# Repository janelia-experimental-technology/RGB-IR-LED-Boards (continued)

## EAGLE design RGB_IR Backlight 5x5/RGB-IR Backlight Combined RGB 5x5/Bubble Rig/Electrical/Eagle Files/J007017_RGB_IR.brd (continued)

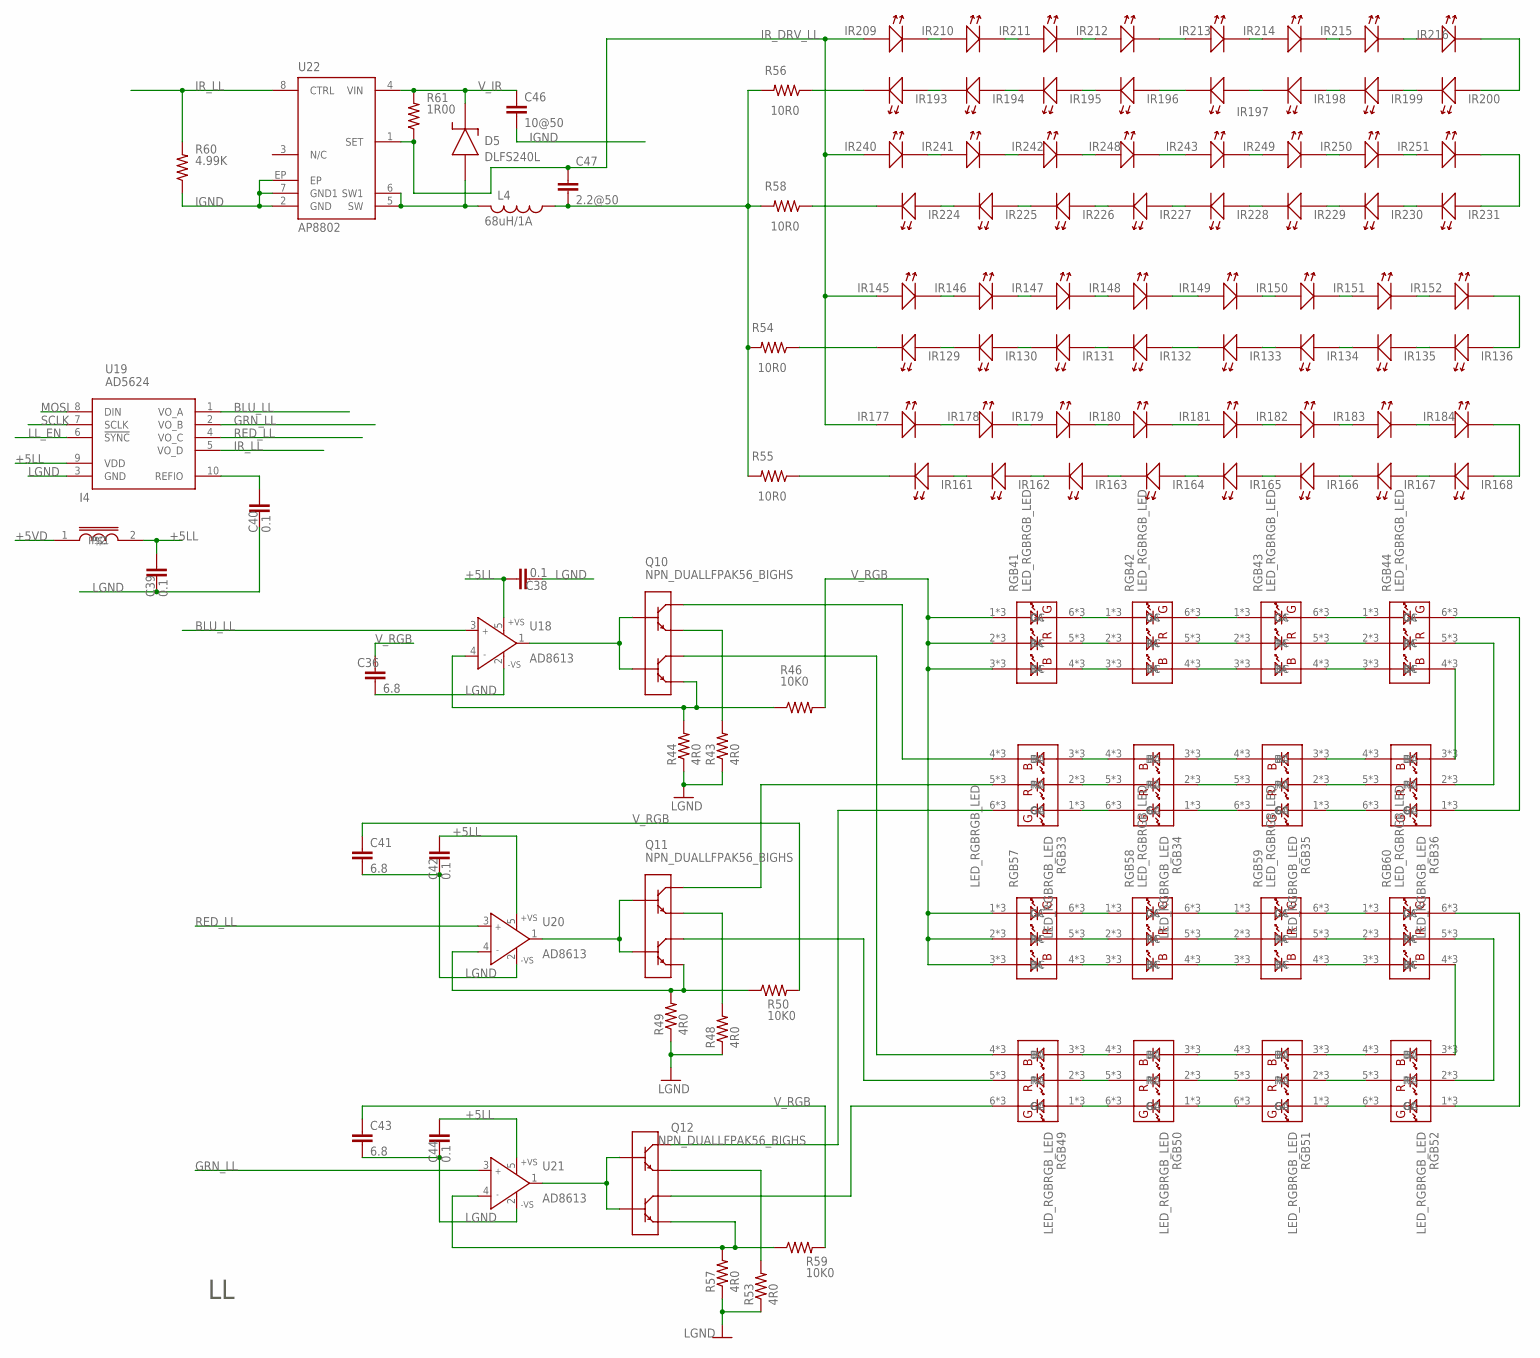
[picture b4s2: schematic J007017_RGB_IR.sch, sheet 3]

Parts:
C36, C41, C43: 6.8; 1210S
C38, C39, C40, C42, C44: 0.1; 0603S
C46: 10@50; 1210S
C47: 2.2@50; 1206S
D5: DLFS240L; PWRDI-123
I4: INDUCTOR0805S; 0805S
IR129: LEDLED_SFH4050_A; LED_SFH4045_HEAT_A
IR130, IR131, IR132, IR133, IR134, IR135, IR145, IR146, IR147, IR148, IR149, IR150, IR151, IR152, IR161, IR162, IR163, IR164, IR165, IR166, IR167, IR168, IR177, IR178, IR179, IR180, IR181, IR182, IR183, IR184, IR193, IR194, IR195, IR196, IR197, IR198, IR199, IR200, IR209, IR210, IR211, IR212, IR213, IR214, IR215, IR216, IR224, IR225, IR226, IR227, IR228, IR229, IR230, IR231, IR240, IR241, IR242, IR243, IR248, IR249, IR250: LEDLED_SFH4050_HEAT; LED_SFH4050_HEAT
IR136, IR251: LEDLED_SFH4050; LED_SFH4050
L4: 68uH/1A; SRU8043
Q10, Q11, Q12: NPN_DUALLFPAK56_BIGHS; LFPAK56_HS2
R43, R44, R48, R49, R53, R57: 4R0; 1812
R46, R50, R59: 10K0; 1206S
R54, R55, R56, R58: 10R0; 1206S
R60: 4.99K; 0805S
R61: 1R00; 1206S
RGB33, RGB34, RGB35, RGB36, RGB41, RGB42, RGB43, RGB44, RGB49, RGB50, RGB51, RGB52, RGB57, RGB58, RGB59, RGB60: LED_RGBRGB_LED; OVSPRGB_HS_FIXED
U18, U20, U21: AD8613; SOT23-5
U19: AD5624; MSOP10
U22: AP8802; SOIC8-EP

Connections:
+5LL: C38.1, C39.1, C42.1, C44.1, I4.2, U18.5 (+VS), U19.9 (VDD), U20.5 (+VS), U21.5 (+VS)
+5VD: I4.1; also elsewhere on the board
BLU_LL: U18.3 (IN+), U19.1 (VO_A)
GRN_LL: U19.2 (VO_B), U21.3 (IN+)
IGND: C46.2, R60.1, U22.2 (GND), U22.7 (GND1), U22.EP; also elsewhere on the board
IR_DRV_LL: C47.1, IR145.A, IR145.A1 (A), IR177.A, IR177.A1 (A), IR209.A, IR209.A1 (A), IR240.A, IR240.A1 (A), R61.1, U22.1 (SET)
IR_LL: R60.2, U19.5 (VO_D), U22.8 (CTRL)
IR_RET_UL1: C47.2, L4.1, R54.2, R55.2, R56.2, R58.2
LGND: C36.2, C38.2, C39.2, C40.2, C41.2, C42.2, C43.2, C44.2, R43.1, R44.1, R48.1, R49.1, R53.1, R57.1, U18.2 (-VS), U19.3 (GND), U20.2 (-VS), U21.2 (-VS); also elsewhere on the board
LL_EN: U19.6 (!SYNC); also elsewhere on the board
MOSI: U19.8 (DIN); also elsewhere on the board
unnamed: IR135.A, IR135.A1 (A), IR136.C (K)
unnamed: IR134.A, IR134.A1 (A), IR135.C (K), IR135.C1 (K)
unnamed: IR133.A, IR133.A1 (A), IR134.C (K), IR134.C1 (K)
unnamed: C40.1, U19.10 (REFIO)
unnamed: IR131.A, IR131.A1 (A), IR132.C (K), IR132.C1 (K)
unnamed: IR130.A, IR130.A1 (A), IR131.C (K), IR131.C1 (K)
unnamed: IR129.A, IR129.A1 (A), IR130.C (K), IR130.C1 (K)
unnamed: IR145.C (K), IR145.C1 (K), IR146.A, IR146.A1 (A)
unnamed: IR146.C (K), IR146.C1 (K), IR147.A, IR147.A1 (A)
unnamed: IR147.C (K), IR147.C1 (K), IR148.A, IR148.A1 (A)
unnamed: IR132.A, IR132.A1 (A), IR133.C (K), IR133.C1 (K)
unnamed: IR167.A, IR167.A1 (A), IR168.C (K), IR168.C1 (K)
unnamed: IR166.A, IR166.A1 (A), IR167.C (K), IR167.C1 (K)
unnamed: IR165.A, IR165.A1 (A), IR166.C (K), IR166.C1 (K)
unnamed: IR164.A, IR164.A1 (A), IR165.C (K), IR165.C1 (K)
unnamed: IR163.A, IR163.A1 (A), IR164.C (K), IR164.C1 (K)
unnamed: IR162.A, IR162.A1 (A), IR163.C (K), IR163.C1 (K)
unnamed: IR161.A, IR161.A1 (A), IR162.C (K), IR162.C1 (K)
unnamed: IR149.C (K), IR149.C1 (K), IR150.A, IR150.A1 (A)
unnamed: IR150.C (K), IR150.C1 (K), IR151.A, IR151.A1 (A)
unnamed: IR151.C (K), IR151.C1 (K), IR152.A, IR152.A1 (A)
unnamed: IR177.C (K), IR177.C1 (K), IR178.A, IR178.A1 (A)
unnamed: IR178.C (K), IR178.C1 (K), IR179.A, IR179.A1 (A)
unnamed: IR179.C (K), IR179.C1 (K), IR180.A, IR180.A1 (A)
unnamed: IR181.C (K), IR181.C1 (K), IR182.A, IR182.A1 (A)
unnamed: IR182.C (K), IR182.C1 (K), IR183.A, IR183.A1 (A)
unnamed: IR183.C (K), IR183.C1 (K), IR184.A, IR184.A1 (A)
unnamed: IR148.C (K), IR148.C1 (K), IR149.A, IR149.A1 (A)
unnamed: IR136.A, IR152.C (K), IR152.C1 (K)
unnamed: IR180.C (K), IR180.C1 (K), IR181.A, IR181.A1 (A)
unnamed: IR168.A, IR168.A1 (A), IR184.C (K), IR184.C1 (K)
unnamed: IR129.C (K), R54.1
unnamed: IR161.C (K), IR161.C1 (K), R55.1
unnamed: IR199.A, IR199.A1 (A), IR200.C (K), IR200.C1 (K)
unnamed: IR198.A, IR198.A1 (A), IR199.C (K), IR199.C1 (K)
unnamed: IR197.A, IR197.A1 (A), IR198.C (K), IR198.C1 (K)
unnamed: IR195.A, IR195.A1 (A), IR196.C (K), IR196.C1 (K)
unnamed: IR194.A, IR194.A1 (A), IR195.C (K), IR195.C1 (K)
unnamed: IR193.A, IR193.A1 (A), IR194.C (K), IR194.C1 (K)
unnamed: IR209.C (K), IR209.C1 (K), IR210.A, IR210.A1 (A)
unnamed: IR210.C (K), IR210.C1 (K), IR211.A, IR211.A1 (A)
unnamed: IR211.C (K), IR211.C1 (K), IR212.A, IR212.A1 (A)
unnamed: IR196.A, IR196.A1 (A), IR197.C (K), IR197.C1 (K)
unnamed: IR230.A, IR230.A1 (A), IR231.C (K), IR231.C1 (K)
unnamed: IR229.A, IR229.A1 (A), IR230.C (K), IR230.C1 (K)
unnamed: IR228.A, IR228.A1 (A), IR229.C (K), IR229.C1 (K)
unnamed: IR227.A, IR227.A1 (A), IR228.C (K), IR228.C1 (K)
unnamed: IR226.A, IR226.A1 (A), IR227.C (K), IR227.C1 (K)
unnamed: IR225.A, IR225.A1 (A), IR226.C (K), IR226.C1 (K)
unnamed: IR224.A, IR224.A1 (A), IR225.C (K), IR225.C1 (K)
unnamed: IR213.C (K), IR213.C1 (K), IR214.A, IR214.A1 (A)
unnamed: IR214.C (K), IR214.C1 (K), IR215.A, IR215.A1 (A)
unnamed: IR215.C (K), IR215.C1 (K), IR216.A, IR216.A1 (A)
unnamed: IR240.C (K), IR240.C1 (K), IR241.A, IR241.A1 (A)
unnamed: IR241.C (K), IR241.C1 (K), IR242.A, IR242.A1 (A)
unnamed: IR242.C (K), IR242.C1 (K), IR248.A, IR248.A1 (A)
unnamed: IR243.C (K), IR243.C1 (K), IR249.A, IR249.A1 (A)
unnamed: IR249.C (K), IR249.C1 (K), IR250.A, IR250.A1 (A)
unnamed: IR250.C (K), IR250.C1 (K), IR251.A
unnamed: IR212.C (K), IR212.C1 (K), IR213.A, IR213.A1 (A)
unnamed: IR200.A, IR200.A1 (A), IR216.C (K), IR216.C1 (K)
unnamed: IR243.A, IR243.A1 (A), IR248.C (K), IR248.C1 (K)
unnamed: IR231.A, IR231.A1 (A), IR251.C (K)
unnamed: IR193.C (K), IR193.C1 (K), R56.1
unnamed: IR224.C (K), IR224.C1 (K), R58.1
unnamed: Q10.3 (E2), R44.2, R46.1, U18.4 (IN-)
unnamed: D5.A, L4.2, U22.5 (SW), U22.6 (SW1)
unnamed: Q11.3 (E2), R49.2, R50.1, U20.4 (IN-)
unnamed: Q11.2 (B1), Q11.4 (B2), U20.1 (OUT)
unnamed: RGB41.6 (GC), RGB41.6A (GC), RGB41.6B (GC), RGB42.1 (GA), RGB42.1A (GA), RGB42.1B (GA)
unnamed: RGB41.5 (RC), RGB41.5A (RC), RGB41.5B (RC), RGB42.2 (RA), RGB42.2A (RA), RGB42.2B (RA)
unnamed: RGB41.4 (BC), RGB41.4A (BC), RGB41.4B (BC), RGB42.3 (BA), RGB42.3A (BA), RGB42.3B (BA)
unnamed: RGB42.6 (GC), RGB42.6A (GC), RGB42.6B (GC), RGB43.1 (GA), RGB43.1A (GA), RGB43.1B (GA)
unnamed: RGB42.5 (RC), RGB42.5A (RC), RGB42.5B (RC), RGB43.2 (RA), RGB43.2A (RA), RGB43.2B (RA)
unnamed: RGB42.4 (BC), RGB42.4A (BC), RGB42.4B (BC), RGB43.3 (BA), RGB43.3A (BA), RGB43.3B (BA)
unnamed: RGB43.6 (GC), RGB43.6A (GC), RGB43.6B (GC), RGB44.1 (GA), RGB44.1A (GA), RGB44.1B (GA)
unnamed: RGB43.5 (RC), RGB43.5A (RC), RGB43.5B (RC), RGB44.2 (RA), RGB44.2A (RA), RGB44.2B (RA)
unnamed: RGB43.4 (BC), RGB43.4A (BC), RGB43.4B (BC), RGB44.3 (BA), RGB44.3A (BA), RGB44.3B (BA)
unnamed: RGB36.1 (GA), RGB36.1A (GA), RGB36.1B (GA), RGB44.6 (GC), RGB44.6A (GC), RGB44.6B (GC)
unnamed: RGB36.2 (RA), RGB36.2A (RA), RGB36.2B (RA), RGB44.5 (RC), RGB44.5A (RC), RGB44.5B (RC)
unnamed: RGB36.3 (BA), RGB36.3A (BA), RGB36.3B (BA), RGB44.4 (BC), RGB44.4A (BC), RGB44.4B (BC)
unnamed: RGB35.1 (GA), RGB35.1A (GA), RGB35.1B (GA), RGB36.6 (GC), RGB36.6A (GC), RGB36.6B (GC)
unnamed: RGB35.2 (RA), RGB35.2A (RA), RGB35.2B (RA), RGB36.5 (RC), RGB36.5A (RC), RGB36.5B (RC)
unnamed: RGB35.3 (BA), RGB35.3A (BA), RGB35.3B (BA), RGB36.4 (BC), RGB36.4A (BC), RGB36.4B (BC)
unnamed: RGB34.1 (GA), RGB34.1A (GA), RGB34.1B (GA), RGB35.6 (GC), RGB35.6A (GC), RGB35.6B (GC)
unnamed: RGB34.2 (RA), RGB34.2A (RA), RGB34.2B (RA), RGB35.5 (RC), RGB35.5A (RC), RGB35.5B (RC)
unnamed: RGB34.3 (BA), RGB34.3A (BA), RGB34.3B (BA), RGB35.4 (BC), RGB35.4A (BC), RGB35.4B (BC)
unnamed: RGB33.1 (GA), RGB33.1A (GA), RGB33.1B (GA), RGB34.6 (GC), RGB34.6A (GC), RGB34.6B (GC)
unnamed: RGB33.2 (RA), RGB33.2A (RA), RGB33.2B (RA), RGB34.5 (RC), RGB34.5A (RC), RGB34.5B (RC)
unnamed: RGB33.3 (BA), RGB33.3A (BA), RGB33.3B (BA), RGB34.4 (BC), RGB34.4A (BC), RGB34.4B (BC)
unnamed: Q12.3 (E2), R57.2, R59.1, U21.4 (IN-)
unnamed: Q12.2 (B1), Q12.4 (B2), U21.1 (OUT)
unnamed: RGB57.6 (GC), RGB57.6A (GC), RGB57.6B (GC), RGB58.1 (GA), RGB58.1A (GA), RGB58.1B (GA)
unnamed: RGB57.5 (RC), RGB57.5A (RC), RGB57.5B (RC), RGB58.2 (RA), RGB58.2A (RA), RGB58.2B (RA)
unnamed: RGB57.4 (BC), RGB57.4A (BC), RGB57.4B (BC), RGB58.3 (BA), RGB58.3A (BA), RGB58.3B (BA)
unnamed: RGB58.6 (GC), RGB58.6A (GC), RGB58.6B (GC), RGB59.1 (GA), RGB59.1A (GA), RGB59.1B (GA)
unnamed: RGB58.5 (RC), RGB58.5A (RC), RGB58.5B (RC), RGB59.2 (RA), RGB59.2A (RA), RGB59.2B (RA)
unnamed: RGB58.4 (BC), RGB58.4A (BC), RGB58.4B (BC), RGB59.3 (BA), RGB59.3A (BA), RGB59.3B (BA)
unnamed: RGB59.6 (GC), RGB59.6A (GC), RGB59.6B (GC), RGB60.1 (GA), RGB60.1A (GA), RGB60.1B (GA)
unnamed: RGB59.5 (RC), RGB59.5A (RC), RGB59.5B (RC), RGB60.2 (RA), RGB60.2A (RA), RGB60.2B (RA)
unnamed: RGB59.4 (BC), RGB59.4A (BC), RGB59.4B (BC), RGB60.3 (BA), RGB60.3A (BA), RGB60.3B (BA)
unnamed: RGB52.1 (GA), RGB52.1A (GA), RGB52.1B (GA), RGB60.6 (GC), RGB60.6A (GC), RGB60.6B (GC)
unnamed: RGB52.2 (RA), RGB52.2A (RA), RGB52.2B (RA), RGB60.5 (RC), RGB60.5A (RC), RGB60.5B (RC)
unnamed: RGB52.3 (BA), RGB52.3A (BA), RGB52.3B (BA), RGB60.4 (BC), RGB60.4A (BC), RGB60.4B (BC)
unnamed: RGB51.1 (GA), RGB51.1A (GA), RGB51.1B (GA), RGB52.6 (GC), RGB52.6A (GC), RGB52.6B (GC)
unnamed: RGB51.2 (RA), RGB51.2A (RA), RGB51.2B (RA), RGB52.5 (RC), RGB52.5A (RC), RGB52.5B (RC)
unnamed: RGB51.3 (BA), RGB51.3A (BA), RGB51.3B (BA), RGB52.4 (BC), RGB52.4A (BC), RGB52.4B (BC)
unnamed: RGB50.1 (GA), RGB50.1A (GA), RGB50.1B (GA), RGB51.6 (GC), RGB51.6A (GC), RGB51.6B (GC)
unnamed: RGB50.2 (RA), RGB50.2A (RA), RGB50.2B (RA), RGB51.5 (RC), RGB51.5A (RC), RGB51.5B (RC)
unnamed: RGB50.3 (BA), RGB50.3A (BA), RGB50.3B (BA), RGB51.4 (BC), RGB51.4A (BC), RGB51.4B (BC)
unnamed: RGB49.1 (GA), RGB49.1A (GA), RGB49.1B (GA), RGB50.6 (GC), RGB50.6A (GC), RGB50.6B (GC)
unnamed: RGB49.2 (RA), RGB49.2A (RA), RGB49.2B (RA), RGB50.5 (RC), RGB50.5A (RC), RGB50.5B (RC)
unnamed: RGB49.3 (BA), RGB49.3A (BA), RGB49.3B (BA), RGB50.4 (BC), RGB50.4A (BC), RGB50.4B (BC)
unnamed: Q10.2 (B1), Q10.4 (B2), U18.1 (OUT)
unnamed: Q10.1 (E1), R43.2
unnamed: Q11.1 (E1), R48.2
unnamed: Q12.1 (E1), R53.2
Q4A: Q10.7 (C1), Q10.8 (C1), Q10.8A (C1), Q10.8B (C1), Q10.8C (C1), Q10.8C1 (C1), Q10.8C2 (C1), Q10.8C3 (C1), Q10.78 (C1), Q10.78A (C1), Q10.78B (C1), RGB33.4 (BC), RGB33.4A (BC), RGB33.4B (BC)
Q4B: Q10.5 (C2), Q10.5A (C2), Q10.5A1 (C2), Q10.5B (C2), Q10.5C (C2), Q10.5C1 (C2), Q10.5C2 (C2), Q10.6 (C2), Q10.56 (C2), Q10.56A (C2), Q10.56B (C2), RGB49.4 (BC), RGB49.4A (BC), RGB49.4B (BC)
Q5A: Q11.7 (C1), Q11.8 (C1), Q11.8A (C1), Q11.8B (C1), Q11.8C (C1), Q11.8C1 (C1), Q11.8C2 (C1), Q11.8C3 (C1), Q11.78 (C1), Q11.78A (C1), Q11.78B (C1), RGB33.5 (RC), RGB33.5A (RC), RGB33.5B (RC)
Q5B: Q11.5 (C2), Q11.5A (C2), Q11.5A1 (C2), Q11.5B (C2), Q11.5C (C2), Q11.5C1 (C2), Q11.5C2 (C2), Q11.6 (C2), Q11.56 (C2), Q11.56A (C2), Q11.56B (C2), RGB49.5 (RC), RGB49.5A (RC), RGB49.5B (RC)
Q6A: Q12.7 (C1), Q12.8 (C1), Q12.8A (C1), Q12.8B (C1), Q12.8C (C1), Q12.8C1 (C1), Q12.8C2 (C1), Q12.8C3 (C1), Q12.78 (C1), Q12.78A (C1), Q12.78B (C1), RGB33.6 (GC), RGB33.6A (GC), RGB33.6B (GC)
Q6B: Q12.5 (C2), Q12.5A (C2), Q12.5A1 (C2), Q12.5B (C2), Q12.5C (C2), Q12.5C1 (C2), Q12.5C2 (C2), Q12.6 (C2), Q12.56 (C2), Q12.56A (C2), Q12.56B (C2), RGB49.6 (GC), RGB49.6A (GC), RGB49.6B (GC)
RED_LL: U19.4 (VO_C), U20.3 (IN+)
SCLK: U19.7 (SCLK); also elsewhere on the board
V_IR: C46.1, D5.K, R61.2, U22.4 (VIN); also elsewhere on the board
V_RGB: C36.1, C41.1, C43.1, R46.2, R50.2, R59.2, RGB41.1 (GA), RGB41.1A (GA), RGB41.1B (GA), RGB41.2 (RA), RGB41.2A (RA), RGB41.2B (RA), RGB41.3 (BA), RGB41.3A (BA), RGB41.3B (BA), RGB57.1 (GA), RGB57.1A (GA), RGB57.1B (GA), RGB57.2 (RA), RGB57.2A (RA), RGB57.2B (RA), RGB57.3 (BA), RGB57.3A (BA), RGB57.3B (BA); also elsewhere on the board

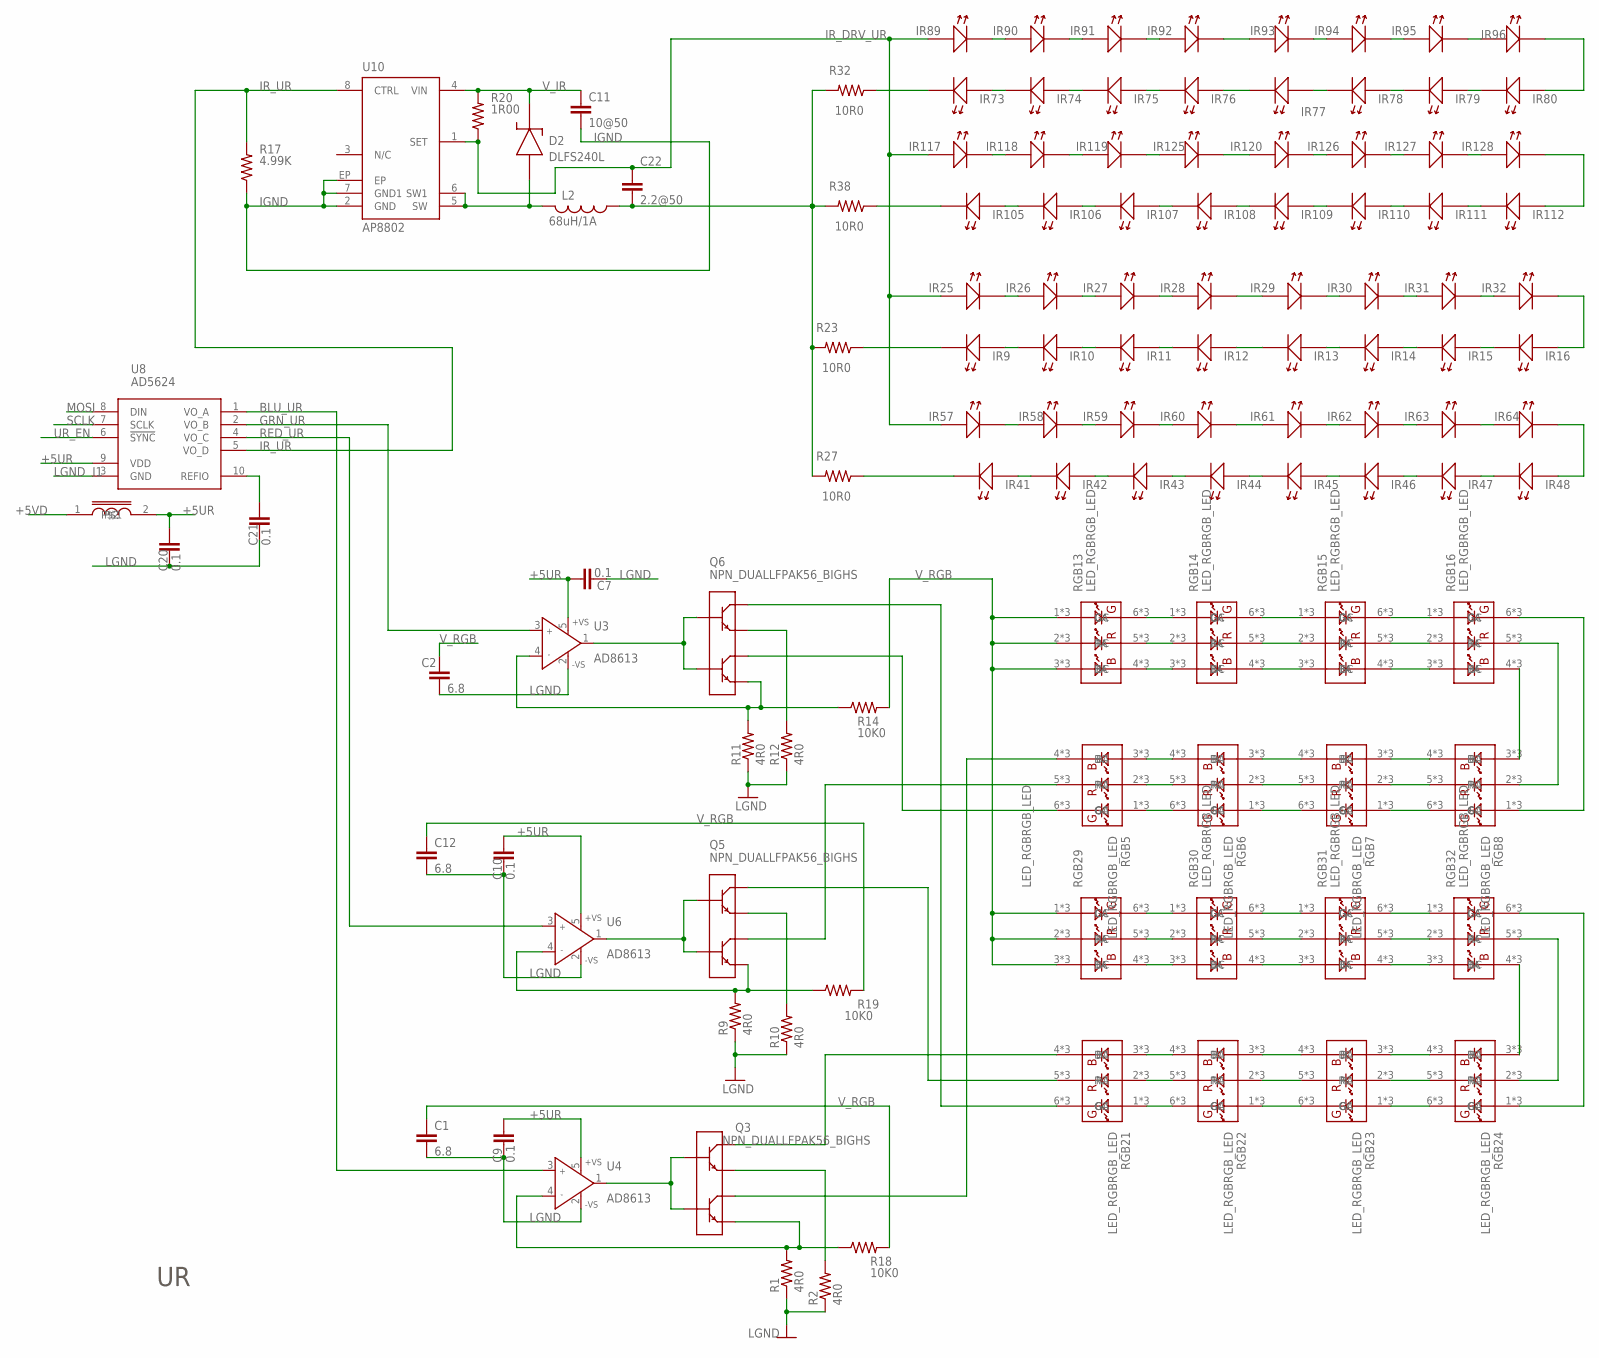
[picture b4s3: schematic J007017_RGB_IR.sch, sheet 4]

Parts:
C1, C2, C12: 6.8; 1210S
C7, C9, C10, C20, C21: 0.1; 0603S
C11: 10@50; 1210S
C22: 2.2@50; 1206S
D2: DLFS240L; PWRDI-123
I1: INDUCTOR0805S; 0805S
IR9, IR10, IR11, IR12, IR13, IR14, IR15, IR16, IR25, IR26, IR27, IR28, IR29, IR30, IR31, IR32, IR41, IR42, IR43, IR44, IR45, IR46, IR47, IR48, IR57, IR58, IR59, IR60, IR61, IR62, IR63, IR64, IR73, IR74, IR75, IR76, IR77, IR78, IR79, IR80, IR89, IR90, IR91, IR92, IR93, IR94, IR95, IR96, IR105, IR107, IR108, IR109, IR110, IR111, IR112, IR118, IR119, IR120, IR125, IR126, IR127: LEDLED_SFH4050_HEAT; LED_SFH4050_HEAT
IR106: LEDLED_SFH4050_C; LED_SFH4050_HEAT_C
IR117, IR128: LEDLED_SFH4050; LED_SFH4050
L2: 68uH/1A; SRU8043
Q3, Q5, Q6: NPN_DUALLFPAK56_BIGHS; LFPAK56_HS2
R1, R2, R9, R10, R11, R12: 4R0; 1812
R14, R18, R19: 10K0; 1206S
R17: 4.99K; 0805S
R20: 1R00; 1206S
R23, R27, R32, R38: 10R0; 1206S
RGB5, RGB6, RGB7, RGB8, RGB13, RGB14, RGB15, RGB16, RGB21, RGB22, RGB23, RGB24, RGB29, RGB30, RGB31, RGB32: LED_RGBRGB_LED; OVSPRGB_HS_FIXED
U3, U4, U6: AD8613; SOT23-5
U8: AD5624; MSOP10
U10: AP8802; SOIC8-EP

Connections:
+5UR: C7.1, C9.1, C10.1, C20.1, I1.2, U3.5 (+VS), U4.5 (+VS), U6.5 (+VS), U8.9 (VDD)
+5VD: I1.1; also elsewhere on the board
BLU_UR: U4.3 (IN+), U8.1 (VO_A)
GRN_UR: U3.3 (IN+), U8.2 (VO_B)
IGND: C11.2, R17.1, U10.2 (GND), U10.7 (GND1), U10.EP; also elsewhere on the board
IR_DRV_UR: C22.1, IR25.A, IR25.A1 (A), IR57.A, IR57.A1 (A), IR89.A, IR89.A1 (A), IR117.A, R20.1, U10.1 (SET)
IR_RET_UL2: C22.2, L2.1, R23.2, R27.2, R32.2, R38.2
IR_UR: R17.2, U8.5 (VO_D), U10.8 (CTRL)
LGND: C1.2, C2.2, C7.2, C9.2, C10.2, C12.2, C20.2, C21.2, R1.1, R2.1, R9.1, R10.1, R11.1, R12.1, U3.2 (-VS), U4.2 (-VS), U6.2 (-VS), U8.3 (GND); also elsewhere on the board
MOSI: U8.8 (DIN); also elsewhere on the board
unnamed: C21.1, U8.10 (REFIO)
unnamed: IR15.A, IR15.A1 (A), IR16.C (K), IR16.C1 (K)
unnamed: IR14.A, IR14.A1 (A), IR15.C (K), IR15.C1 (K)
unnamed: IR13.A, IR13.A1 (A), IR14.C (K), IR14.C1 (K)
unnamed: IR11.A, IR11.A1 (A), IR12.C (K), IR12.C1 (K)
unnamed: IR10.A, IR10.A1 (A), IR11.C (K), IR11.C1 (K)
unnamed: IR9.A, IR9.A1 (A), IR10.C (K), IR10.C1 (K)
unnamed: IR25.C (K), IR25.C1 (K), IR26.A, IR26.A1 (A)
unnamed: IR26.C (K), IR26.C1 (K), IR27.A, IR27.A1 (A)
unnamed: IR27.C (K), IR27.C1 (K), IR28.A, IR28.A1 (A)
unnamed: IR12.A, IR12.A1 (A), IR13.C (K), IR13.C1 (K)
unnamed: IR47.A, IR47.A1 (A), IR48.C (K), IR48.C1 (K)
unnamed: IR46.A, IR46.A1 (A), IR47.C (K), IR47.C1 (K)
unnamed: IR45.A, IR45.A1 (A), IR46.C (K), IR46.C1 (K)
unnamed: IR44.A, IR44.A1 (A), IR45.C (K), IR45.C1 (K)
unnamed: IR43.A, IR43.A1 (A), IR44.C (K), IR44.C1 (K)
unnamed: IR42.A, IR42.A1 (A), IR43.C (K), IR43.C1 (K)
unnamed: IR41.A, IR41.A1 (A), IR42.C (K), IR42.C1 (K)
unnamed: IR29.C (K), IR29.C1 (K), IR30.A, IR30.A1 (A)
unnamed: IR30.C (K), IR30.C1 (K), IR31.A, IR31.A1 (A)
unnamed: IR31.C (K), IR31.C1 (K), IR32.A, IR32.A1 (A)
unnamed: IR57.C (K), IR57.C1 (K), IR58.A, IR58.A1 (A)
unnamed: IR58.C (K), IR58.C1 (K), IR59.A, IR59.A1 (A)
unnamed: IR59.C (K), IR59.C1 (K), IR60.A, IR60.A1 (A)
unnamed: IR61.C (K), IR61.C1 (K), IR62.A, IR62.A1 (A)
unnamed: IR62.C (K), IR62.C1 (K), IR63.A, IR63.A1 (A)
unnamed: IR63.C (K), IR63.C1 (K), IR64.A, IR64.A1 (A)
unnamed: IR28.C (K), IR28.C1 (K), IR29.A, IR29.A1 (A)
unnamed: IR16.A, IR16.A1 (A), IR32.C (K), IR32.C1 (K)
unnamed: IR60.C (K), IR60.C1 (K), IR61.A, IR61.A1 (A)
unnamed: IR48.A, IR48.A1 (A), IR64.C (K), IR64.C1 (K)
unnamed: IR9.C (K), IR9.C1 (K), R23.1
unnamed: IR41.C (K), IR41.C1 (K), R27.1
unnamed: IR79.A, IR79.A1 (A), IR80.C (K), IR80.C1 (K)
unnamed: IR78.A, IR78.A1 (A), IR79.C (K), IR79.C1 (K)
unnamed: IR77.A, IR77.A1 (A), IR78.C (K), IR78.C1 (K)
unnamed: IR75.A, IR75.A1 (A), IR76.C (K), IR76.C1 (K)
unnamed: IR74.A, IR74.A1 (A), IR75.C (K), IR75.C1 (K)
unnamed: IR73.A, IR73.A1 (A), IR74.C (K), IR74.C1 (K)
unnamed: IR89.C (K), IR89.C1 (K), IR90.A, IR90.A1 (A)
unnamed: IR90.C (K), IR90.C1 (K), IR91.A, IR91.A1 (A)
unnamed: IR91.C (K), IR91.C1 (K), IR92.A, IR92.A1 (A)
unnamed: IR76.A, IR76.A1 (A), IR77.C (K), IR77.C1 (K)
unnamed: IR111.A, IR111.A1 (A), IR112.C (K), IR112.C1 (K)
unnamed: IR110.A, IR110.A1 (A), IR111.C (K), IR111.C1 (K)
unnamed: IR109.A, IR109.A1 (A), IR110.C (K), IR110.C1 (K)
unnamed: IR108.A, IR108.A1 (A), IR109.C (K), IR109.C1 (K)
unnamed: IR107.A, IR107.A1 (A), IR108.C (K), IR108.C1 (K)
unnamed: IR106.A, IR107.C (K), IR107.C1 (K)
unnamed: IR105.A, IR105.A1 (A), IR106.C (K), IR106.C1 (K)
unnamed: IR93.C (K), IR93.C1 (K), IR94.A, IR94.A1 (A)
unnamed: IR94.C (K), IR94.C1 (K), IR95.A, IR95.A1 (A)
unnamed: IR95.C (K), IR95.C1 (K), IR96.A, IR96.A1 (A)
unnamed: IR117.C (K), IR118.A, IR118.A1 (A)
unnamed: IR118.C (K), IR118.C1 (K), IR119.A, IR119.A1 (A)
unnamed: IR119.C (K), IR119.C1 (K), IR125.A, IR125.A1 (A)
unnamed: IR120.C (K), IR120.C1 (K), IR126.A, IR126.A1 (A)
unnamed: IR126.C (K), IR126.C1 (K), IR127.A, IR127.A1 (A)
unnamed: IR127.C (K), IR127.C1 (K), IR128.A
unnamed: IR92.C (K), IR92.C1 (K), IR93.A, IR93.A1 (A)
unnamed: IR80.A, IR80.A1 (A), IR96.C (K), IR96.C1 (K)
unnamed: IR120.A, IR120.A1 (A), IR125.C (K), IR125.C1 (K)
unnamed: IR112.A, IR112.A1 (A), IR128.C (K)
unnamed: IR73.C (K), IR73.C1 (K), R32.1
unnamed: IR105.C (K), IR105.C1 (K), R38.1
unnamed: Q6.3 (E2), R11.2, R14.1, U3.4 (IN-)
unnamed: D2.A, L2.2, U10.5 (SW), U10.6 (SW1)
unnamed: Q5.3 (E2), R9.2, R19.1, U6.4 (IN-)
unnamed: Q5.2 (B1), Q5.4 (B2), U6.1 (OUT)
unnamed: RGB13.6 (GC), RGB13.6A (GC), RGB13.6B (GC), RGB14.1 (GA), RGB14.1A (GA), RGB14.1B (GA)
unnamed: RGB13.5 (RC), RGB13.5A (RC), RGB13.5B (RC), RGB14.2 (RA), RGB14.2A (RA), RGB14.2B (RA)
unnamed: RGB13.4 (BC), RGB13.4A (BC), RGB13.4B (BC), RGB14.3 (BA), RGB14.3A (BA), RGB14.3B (BA)
unnamed: RGB14.6 (GC), RGB14.6A (GC), RGB14.6B (GC), RGB15.1 (GA), RGB15.1A (GA), RGB15.1B (GA)
unnamed: RGB14.5 (RC), RGB14.5A (RC), RGB14.5B (RC), RGB15.2 (RA), RGB15.2A (RA), RGB15.2B (RA)
unnamed: RGB14.4 (BC), RGB14.4A (BC), RGB14.4B (BC), RGB15.3 (BA), RGB15.3A (BA), RGB15.3B (BA)
unnamed: RGB15.6 (GC), RGB15.6A (GC), RGB15.6B (GC), RGB16.1 (GA), RGB16.1A (GA), RGB16.1B (GA)
unnamed: RGB15.5 (RC), RGB15.5A (RC), RGB15.5B (RC), RGB16.2 (RA), RGB16.2A (RA), RGB16.2B (RA)
unnamed: RGB15.4 (BC), RGB15.4A (BC), RGB15.4B (BC), RGB16.3 (BA), RGB16.3A (BA), RGB16.3B (BA)
unnamed: RGB8.1 (GA), RGB8.1A (GA), RGB8.1B (GA), RGB16.6 (GC), RGB16.6A (GC), RGB16.6B (GC)
unnamed: RGB8.2 (RA), RGB8.2A (RA), RGB8.2B (RA), RGB16.5 (RC), RGB16.5A (RC), RGB16.5B (RC)
unnamed: RGB8.3 (BA), RGB8.3A (BA), RGB8.3B (BA), RGB16.4 (BC), RGB16.4A (BC), RGB16.4B (BC)
unnamed: RGB7.1 (GA), RGB7.1A (GA), RGB7.1B (GA), RGB8.6 (GC), RGB8.6A (GC), RGB8.6B (GC)
unnamed: RGB7.2 (RA), RGB7.2A (RA), RGB7.2B (RA), RGB8.5 (RC), RGB8.5A (RC), RGB8.5B (RC)
unnamed: RGB7.3 (BA), RGB7.3A (BA), RGB7.3B (BA), RGB8.4 (BC), RGB8.4A (BC), RGB8.4B (BC)
unnamed: RGB6.1 (GA), RGB6.1A (GA), RGB6.1B (GA), RGB7.6 (GC), RGB7.6A (GC), RGB7.6B (GC)
unnamed: RGB6.2 (RA), RGB6.2A (RA), RGB6.2B (RA), RGB7.5 (RC), RGB7.5A (RC), RGB7.5B (RC)
unnamed: RGB6.3 (BA), RGB6.3A (BA), RGB6.3B (BA), RGB7.4 (BC), RGB7.4A (BC), RGB7.4B (BC)
unnamed: RGB5.1 (GA), RGB5.1A (GA), RGB5.1B (GA), RGB6.6 (GC), RGB6.6A (GC), RGB6.6B (GC)
unnamed: RGB5.2 (RA), RGB5.2A (RA), RGB5.2B (RA), RGB6.5 (RC), RGB6.5A (RC), RGB6.5B (RC)
unnamed: RGB5.3 (BA), RGB5.3A (BA), RGB5.3B (BA), RGB6.4 (BC), RGB6.4A (BC), RGB6.4B (BC)
unnamed: Q3.3 (E2), R1.2, R18.1, U4.4 (IN-)
unnamed: Q3.2 (B1), Q3.4 (B2), U4.1 (OUT)
unnamed: RGB29.6 (GC), RGB29.6A (GC), RGB29.6B (GC), RGB30.1 (GA), RGB30.1A (GA), RGB30.1B (GA)
unnamed: RGB29.5 (RC), RGB29.5A (RC), RGB29.5B (RC), RGB30.2 (RA), RGB30.2A (RA), RGB30.2B (RA)
unnamed: RGB29.4 (BC), RGB29.4A (BC), RGB29.4B (BC), RGB30.3 (BA), RGB30.3A (BA), RGB30.3B (BA)
unnamed: RGB30.6 (GC), RGB30.6A (GC), RGB30.6B (GC), RGB31.1 (GA), RGB31.1A (GA), RGB31.1B (GA)
unnamed: RGB30.5 (RC), RGB30.5A (RC), RGB30.5B (RC), RGB31.2 (RA), RGB31.2A (RA), RGB31.2B (RA)
unnamed: RGB30.4 (BC), RGB30.4A (BC), RGB30.4B (BC), RGB31.3 (BA), RGB31.3A (BA), RGB31.3B (BA)
unnamed: RGB31.6 (GC), RGB31.6A (GC), RGB31.6B (GC), RGB32.1 (GA), RGB32.1A (GA), RGB32.1B (GA)
unnamed: RGB31.5 (RC), RGB31.5A (RC), RGB31.5B (RC), RGB32.2 (RA), RGB32.2A (RA), RGB32.2B (RA)
unnamed: RGB31.4 (BC), RGB31.4A (BC), RGB31.4B (BC), RGB32.3 (BA), RGB32.3A (BA), RGB32.3B (BA)
unnamed: RGB24.1 (GA), RGB24.1A (GA), RGB24.1B (GA), RGB32.6 (GC), RGB32.6A (GC), RGB32.6B (GC)
unnamed: RGB24.2 (RA), RGB24.2A (RA), RGB24.2B (RA), RGB32.5 (RC), RGB32.5A (RC), RGB32.5B (RC)
unnamed: RGB24.3 (BA), RGB24.3A (BA), RGB24.3B (BA), RGB32.4 (BC), RGB32.4A (BC), RGB32.4B (BC)
unnamed: RGB23.1 (GA), RGB23.1A (GA), RGB23.1B (GA), RGB24.6 (GC), RGB24.6A (GC), RGB24.6B (GC)
unnamed: RGB23.2 (RA), RGB23.2A (RA), RGB23.2B (RA), RGB24.5 (RC), RGB24.5A (RC), RGB24.5B (RC)
unnamed: RGB23.3 (BA), RGB23.3A (BA), RGB23.3B (BA), RGB24.4 (BC), RGB24.4A (BC), RGB24.4B (BC)
unnamed: RGB22.1 (GA), RGB22.1A (GA), RGB22.1B (GA), RGB23.6 (GC), RGB23.6A (GC), RGB23.6B (GC)
unnamed: RGB22.2 (RA), RGB22.2A (RA), RGB22.2B (RA), RGB23.5 (RC), RGB23.5A (RC), RGB23.5B (RC)
unnamed: RGB22.3 (BA), RGB22.3A (BA), RGB22.3B (BA), RGB23.4 (BC), RGB23.4A (BC), RGB23.4B (BC)
unnamed: RGB21.1 (GA), RGB21.1A (GA), RGB21.1B (GA), RGB22.6 (GC), RGB22.6A (GC), RGB22.6B (GC)
unnamed: RGB21.2 (RA), RGB21.2A (RA), RGB21.2B (RA), RGB22.5 (RC), RGB22.5A (RC), RGB22.5B (RC)
unnamed: RGB21.3 (BA), RGB21.3A (BA), RGB21.3B (BA), RGB22.4 (BC), RGB22.4A (BC), RGB22.4B (BC)
unnamed: Q6.2 (B1), Q6.4 (B2), U3.1 (OUT)
unnamed: Q6.1 (E1), R12.2
unnamed: Q5.1 (E1), R10.2
unnamed: Q3.1 (E1), R2.2
Q7A: Q6.7 (C1), Q6.8 (C1), Q6.8A (C1), Q6.8B (C1), Q6.8C (C1), Q6.8C1 (C1), Q6.8C2 (C1), Q6.8C3 (C1), Q6.78 (C1), Q6.78A (C1), Q6.78B (C1), RGB21.6 (GC), RGB21.6A (GC), RGB21.6B (GC)
Q7B: Q6.5 (C2), Q6.5A (C2), Q6.5A1 (C2), Q6.5B (C2), Q6.5C (C2), Q6.5C1 (C2), Q6.5C2 (C2), Q6.6 (C2), Q6.56 (C2), Q6.56A (C2), Q6.56B (C2), RGB5.6 (GC), RGB5.6A (GC), RGB5.6B (GC)
Q8A: Q5.7 (C1), Q5.8 (C1), Q5.8A (C1), Q5.8B (C1), Q5.8C (C1), Q5.8C1 (C1), Q5.8C2 (C1), Q5.8C3 (C1), Q5.78 (C1), Q5.78A (C1), Q5.78B (C1), RGB21.5 (RC), RGB21.5A (RC), RGB21.5B (RC)
Q8B: Q5.5 (C2), Q5.5A (C2), Q5.5A1 (C2), Q5.5B (C2), Q5.5C (C2), Q5.5C1 (C2), Q5.5C2 (C2), Q5.6 (C2), Q5.56 (C2), Q5.56A (C2), Q5.56B (C2), RGB5.5 (RC), RGB5.5A (RC), RGB5.5B (RC)
Q9A: Q3.7 (C1), Q3.8 (C1), Q3.8A (C1), Q3.8B (C1), Q3.8C (C1), Q3.8C1 (C1), Q3.8C2 (C1), Q3.8C3 (C1), Q3.78 (C1), Q3.78A (C1), Q3.78B (C1), RGB21.4 (BC), RGB21.4A (BC), RGB21.4B (BC)
Q9B: Q3.5 (C2), Q3.5A (C2), Q3.5A1 (C2), Q3.5B (C2), Q3.5C (C2), Q3.5C1 (C2), Q3.5C2 (C2), Q3.6 (C2), Q3.56 (C2), Q3.56A (C2), Q3.56B (C2), RGB5.4 (BC), RGB5.4A (BC), RGB5.4B (BC)
RED_UR: U6.3 (IN+), U8.4 (VO_C)
SCLK: U8.7 (SCLK); also elsewhere on the board
UR_EN: U8.6 (!SYNC); also elsewhere on the board
V_IR: C11.1, D2.K, R20.2, U10.4 (VIN); also elsewhere on the board
V_RGB: C1.1, C2.1, C12.1, R14.2, R18.2, R19.2, RGB13.1 (GA), RGB13.1A (GA), RGB13.1B (GA), RGB13.2 (RA), RGB13.2A (RA), RGB13.2B (RA), RGB13.3 (BA), RGB13.3A (BA), RGB13.3B (BA), RGB29.1 (GA), RGB29.1A (GA), RGB29.1B (GA), RGB29.2 (RA), RGB29.2A (RA), RGB29.2B (RA), RGB29.3 (BA), RGB29.3A (BA), RGB29.3B (BA); also elsewhere on the board
